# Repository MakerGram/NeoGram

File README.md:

# NeoGram v0.0.1α 🎨

NeoGram is an ESP8266 based Open Source Hardware  Development board aimed to provide experiments on NeoPixels (WS2812B) using ESP8266. 

NeoGram is Powerd by [ESP8266-12E Module](Documents/ESP12E-Datasheet.pdf) which is encapsulates <b>Tensilica L106</b> integrates industry-leading ultra low power 32-bit MCU micro, with the 16-bit short mode,
Clock speed support 80 MHz, 160 MHz, supports the RTOS, integrated Wi-Fi MAC/BB/RF/PA/LNA, on-board antenna. The 12 of the  <b>WS2812B</b> can be progarmme indvidualy as maker wish to make there project colorfull 🌈.  

###  Features 

* 12 x Programmble WS2812B
* Plug and Play
* Inbuilt WiFi
* Inbuilt USB to UART
* Inbuild Voltage Regulator
* Reset button
* Power led
* MicroUSB port for programming and debugging 
* USB port can act like serial port, keyboard, mouse, joystick or MIDI!
* Powerd by ESP8266-12E - 32 bit, running 3.3v at 160 MHz
* Arduino Comptable 
* Micropython Compatble
* OpenSource Hardware ❤️

<br>

<hr>

## Schematic 

The [NeoGram Schematic](Hardware) Divided into Four Sections.

* ESP8266 Main Module
* WS2812B LED Array
* USB to UART
* Power Section

<hr>

## ESP8266

The ESP8266 processor from Espressif is an 80 MHz microcontroller with a full WiFi front-end (both as client and access point) and TCP/IP stack with DNS support as well. While this chip has been very popular, its also been very difficult to use. Most of the low cost modules are not breadboard friendly, don't have an onboard 1000mA 3.3V regulator or level shifting.

The NeoGram comes with a onboard 1000mA 3.3v regulator with Arduino/MicroPython Support. 🎉

The module supports standard IEEE802.11 b/g/n agreement, complete TCP/IP protocol stack. Users can use the
add modules to an existing device networking, or building a separate network controller , so It's very conpatable for Internet Of Things project. 

<hr>

## WS2812b  

<b>NeoGram</b> comes with 12 programable WS2812B a.k.a NeoPixel leds. NeoPixel” is Adafruit’s brand for individually-addressable RGB color pixels and strips based on the WS2812, WS2811 and SK6812 LED/drivers, using a single-wire control protocol. 

[WS2812B](Documents/WS2812B.pdf) is a intelligent control LED light source that the control circuit and RGB chip are integrated in
a package of 5050 components. It internal include intelligent digital port data latch and signal reshaping ampli
fication drive circuit. Also include a precision internal oscillator and a 12V voltage programmable constant curr
e-nt control part, effectively ensuring the pixel point light color height consisten.

<hr>

## USB to UART

NeoGram using [FT230x](Documents/ft230x.pdf). The FT230X is a USB to serial UART interface with optimised pin count for
smaller PCB designs. It act as a USB to asynchronous serial data
transfer interface and  No USB specific firmware programming required for the NeoGram. It's ahve Transmit and receive LED drive signals with dev board. 

The FTDI can act as an has an debug port so you can plug in an USB or console cable to upload software and read/write debugging information via the UART. When you're done with your coding, remove the cable, and this little module can be embeded into your project box.

<hr>

## Power

NeoGram comes with onboard 1000mA 3.3V regulator, so we can directly connect USB power supply without any regulator or level shifting. The Power section based on the [LM1117](Documents/lm1117.pdf), it's a The LM117 and LM317-N series of adjustable 3-pin positive voltage regulators are capable of supplying in excess of 1.5 A over a 1.25-V to 37-V output range and a wide temperature range.  we also attached 0.1uf input and output filter capacitors.

<hr><hr>

## Hero Shot

<hr>
<hr>

## Resource
* [Component Datasheets](Documents)
* [PCB Design Files](Hardware)
* [PCB Manufacturing File](Hardware/Manufacturing-File)

<hr>

## Logs

* Jan 2020: Concept and Design
* Jan 2020: Completed PCB Design
* Feb 2020: Complted PCB Fabrication 

<hr>

## To-Do

- [x] PCB Desiging.
- [x] PCB Fabrication.
- [ ] Source Components.
- [ ] Solder Components.
- [ ] Add Custom Board Definition. 

<hr>

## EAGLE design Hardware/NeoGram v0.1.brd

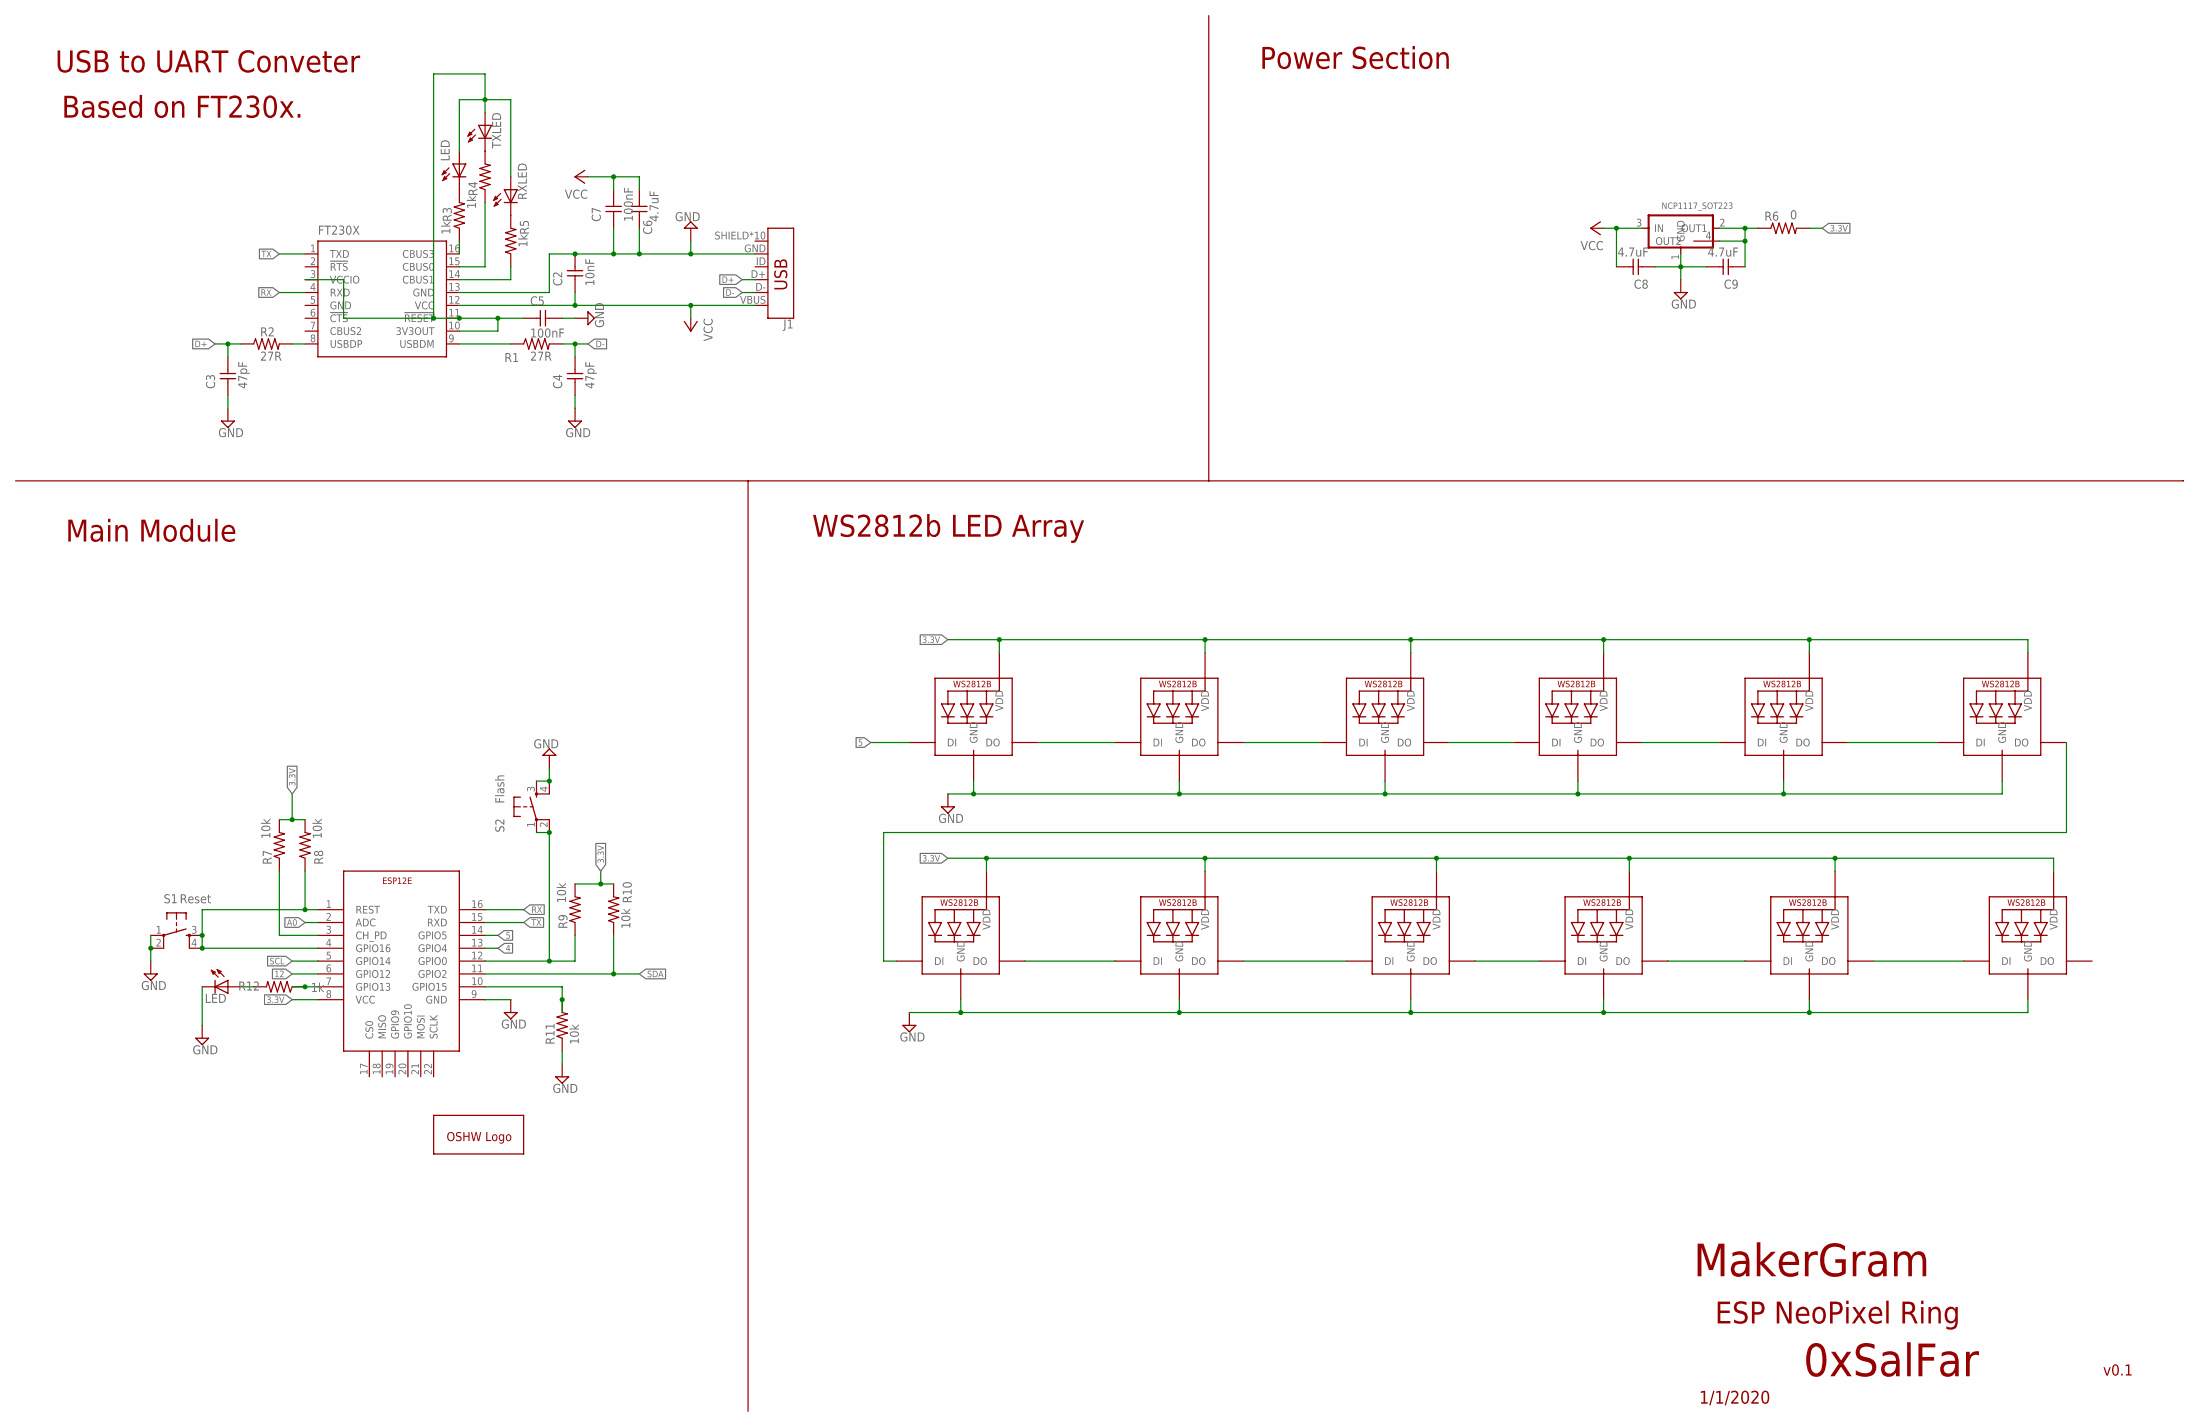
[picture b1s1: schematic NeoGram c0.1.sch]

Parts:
C2: 10nF; C1206FAB
C3, C4: 47pF; C1206FAB
C5, C7: 100nF; C1206FAB
C6, C8, C9: 4.7uF; C1206FAB
FT230X: FT230XS; SSOP16
GOLD_ORB_SM1: OSHWLOGOLOGO8MM; OSHW_8MM
ILED: LED; LED1206
J1: USB_MICRO-B_HALF_PTH_MILL; USB-MICROB-PTH-MILL
LED: LED; LED1206
LED1, LED2, LED3, LED4, LED5, LED6, LED7, LED8, LED9, LED10, LED11, LED12: WS2812B5050; WS2812B
NCP1117: NCP1117_SOT223; SOT223
R1, R2: 27R; R1206
R3, R4, R5, R12: 1k; R1206
R6: 0; R1206
R7, R8, R9, R10, R11: 10k; R1206
RX: RXLED; LED1206
S1: Reset; 6MM_SWITCH
S2: Flash; 6MM_SWITCH
SJR1: ESP-12EESP12E; ESP-12E-SOC
TX: TXLED; LED1206

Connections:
3.3V: LED1.1-VDD (VDD), LED2.1-VDD (VDD), LED3.1-VDD (VDD), LED4.1-VDD (VDD), LED5.1-VDD (VDD), LED6.1-VDD (VDD), LED7.1-VDD (VDD), LED8.1-VDD (VDD), LED9.1-VDD (VDD), LED10.1-VDD (VDD), LED11.1-VDD (VDD), LED12.1-VDD (VDD), R6.2, R7.2, R8.2, R9.2, R10.2, SJR1.8 (VCC)
4: SJR1.13 (GPIO4)
5: LED1.4-DIN (DI), SJR1.14 (GPIO5)
12: SJR1.6 (GPIO12)
A0: SJR1.2 (ADC)
D+: C3.2, J1.D+, R2.1
D-: C4.2, J1.D-, R1.2
GND: C2.2, C3.1, C4.1, C5.2, C6.1, C7.1, C8.1, C9.2, FT230X.5 (GND), FT230X.13 (GND), ILED.2 (C), J1.GND, LED1.3-GND (GND), LED2.3-GND (GND), LED3.3-GND (GND), LED4.3-GND (GND), LED5.3-GND (GND), LED6.3-GND (GND), LED7.3-GND (GND), LED8.3-GND (GND), LED9.3-GND (GND), LED10.3-GND (GND), LED11.3-GND (GND), LED12.3-GND (GND), NCP1117.1 (GND), R11.1, S1.1, S1.2 (P1), S2.3 (S), S2.4 (S1), SJR1.9 (GND)
unnamed: FT230X.9 (USBDM), R1.1
unnamed: FT230X.8 (USBDP), R2.2
unnamed: R8.1, S1.3 (S), S1.4 (S1), SJR1.1 (REST), SJR1.4 (GPIO16)
unnamed: C5.1, FT230X.3 (VCCIO), FT230X.10 (3V3OUT), FT230X.11 (!RESET), LED.1 (A), RX.1 (A), TX.1 (A)
unnamed: R7.1, SJR1.3 (CH_PD)
unnamed: FT230X.16 (CBUS3), R3.1
unnamed: FT230X.15 (CBUS0), R4.1
unnamed: FT230X.14 (CBUS1), R5.1
unnamed: R5.2, RX.2 (C)
unnamed: R4.2, TX.2 (C)
unnamed: C9.1, NCP1117.2 (OUT1), NCP1117.4 (OUT2), R6.1
unnamed: R9.1, S2.1, S2.2 (P1), SJR1.12 (GPIO0)
unnamed: LED.2 (C), R3.2
unnamed: R11.2, SJR1.10 (GPIO15)
unnamed: LED1.2-DOUT (DO), LED2.4-DIN (DI)
unnamed: R12.1, SJR1.7 (GPIO13)
unnamed: ILED.1 (A), R12.2
unnamed: LED2.2-DOUT (DO), LED4.4-DIN (DI)
unnamed: LED4.2-DOUT (DO), LED6.4-DIN (DI)
unnamed: LED6.2-DOUT (DO), LED8.4-DIN (DI)
unnamed: LED3.4-DIN (DI), LED8.2-DOUT (DO)
unnamed: LED5.2-DOUT (DO), LED7.4-DIN (DI)
unnamed: LED7.2-DOUT (DO), LED10.4-DIN (DI)
unnamed: LED9.4-DIN (DI), LED10.2-DOUT (DO)
unnamed: LED9.2-DOUT (DO), LED12.4-DIN (DI)
unnamed: LED11.4-DIN (DI), LED12.2-DOUT (DO)
unnamed: LED3.2-DOUT (DO), LED5.4-DIN (DI)
RX: FT230X.4 (RXD), SJR1.16 (TXD)
SCL: SJR1.5 (GPIO14)
SDA: R10.1, SJR1.11 (GPIO2)
TX: FT230X.1 (TXD), SJR1.15 (RXD)
VCC: C2.1, C6.2, C7.2, C8.2, FT230X.12 (VCC), J1.VBUS, NCP1117.3 (IN)

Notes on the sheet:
MakerGram
ESP NeoPixel Ring
1/1/2020
0xSalFar
v0.1
USB to UART Conveter
Based on FT230x.
Power Section
Main Module
WS2812b LED Array

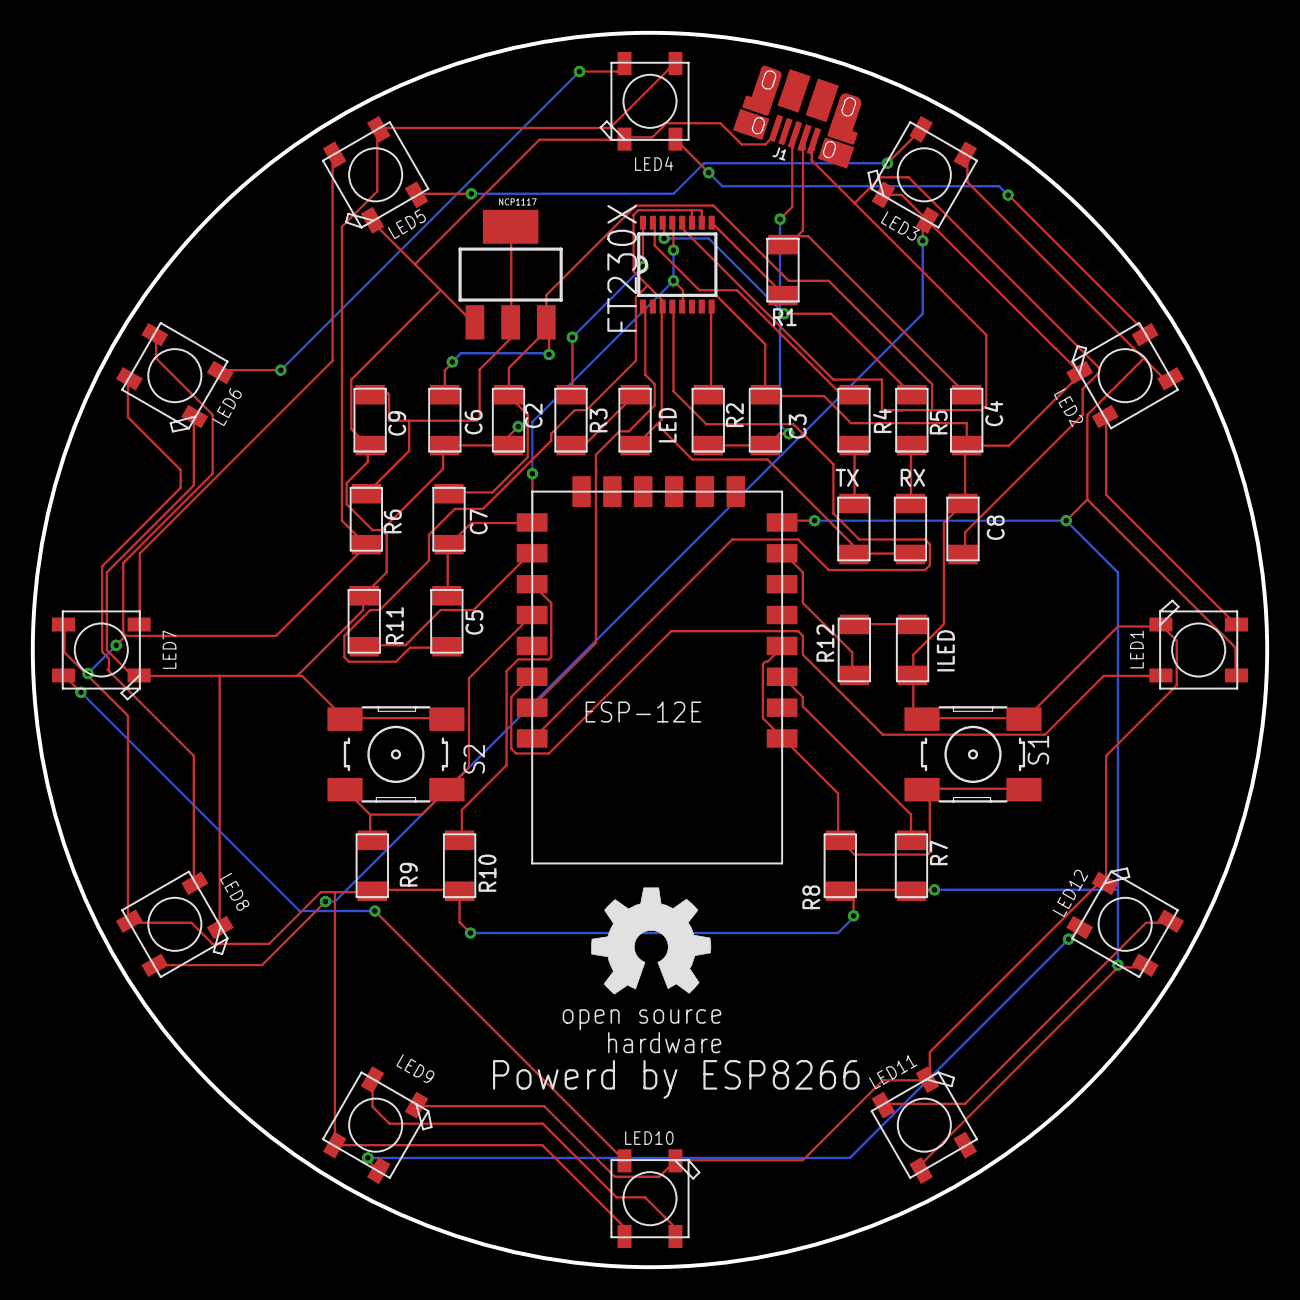
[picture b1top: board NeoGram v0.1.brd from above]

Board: 2 copper layers, 80.0 x 80.0 mm, 44 parts (0 on the bottom side), 36 nets.

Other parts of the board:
U$1: MGLOGO

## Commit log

2020-04-26 add neoGram to
2020-04-26 add neoGram top
2020-04-26 emoji
2020-04-26 add esp8266 datasheet
2020-04-26 add ws2812b
2020-04-27 aligned image center
2020-04-27 add features
2020-04-27 added features
2020-04-27 added verison
2020-04-27 add sch img
2020-04-27 add esp8266 d0c
2020-04-27 fix broken link
2020-04-27 added neo pixel
2020-04-27 added neo pixel led
2020-04-27 add ftdi docs
2020-04-27 add ftdi
2020-04-27 add led array
2020-04-27 add ToDO
2020-04-27 hero shot
2020-04-27 add Software/Libraries
2020-04-28 add verison
2020-05-09 Create license
2020-05-09 Rename license to License.md
2020-09-12 Set theme jekyll-theme-cayman

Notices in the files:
parts and their libraries:
SparkFun-Connectors: Licensing: Creative Commons ShareAlike 4.0 International - https://creativecommons.org/licenses/by-sa/4.0
